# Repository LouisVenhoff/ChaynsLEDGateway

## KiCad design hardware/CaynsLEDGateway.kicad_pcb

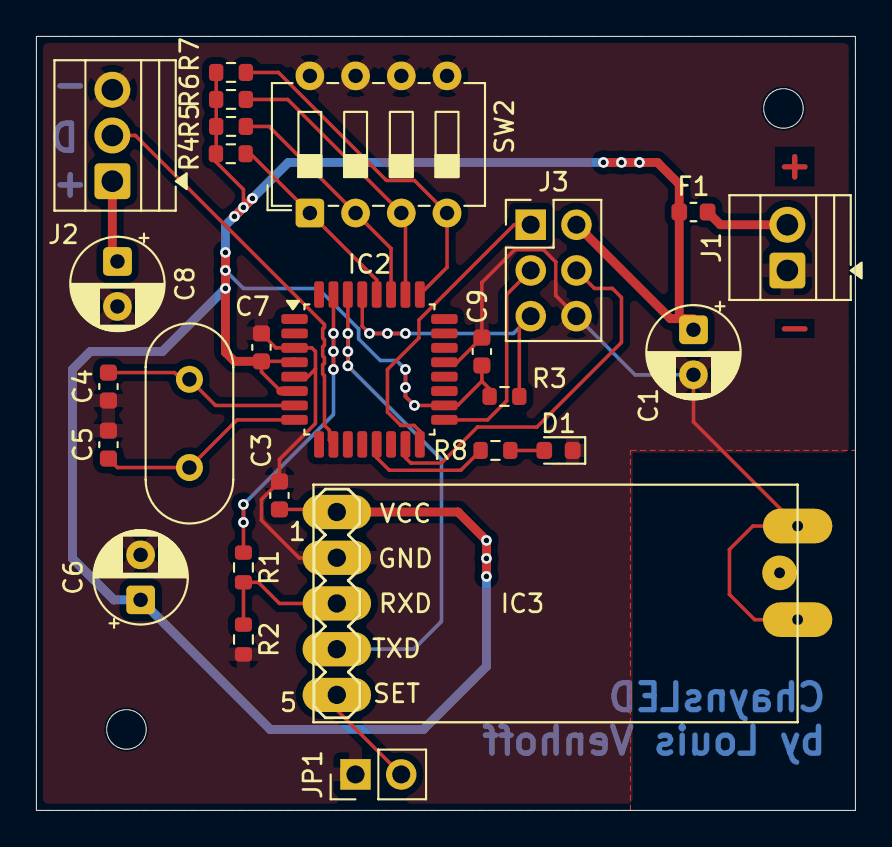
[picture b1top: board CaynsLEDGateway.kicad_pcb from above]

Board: 2 copper layers, 45.5 x 43.0 mm, 28 parts (0 on the bottom side), 21 nets.

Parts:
C1: 100uF; CP_Radial_D5.0mm_P2.50mm
C3, C7, C9: 100n; C_0603_1608Metric
C4, C5: 22pF; C_0603_1608Metric
C6, C8: 47uF; CP_Radial_D5.0mm_P2.50mm
D1: LED Red; LED_0603_1608Metric
F1: 1,5A; Fuse_0603_1608Metric
H1, H2: M2; MountingHole_2.2mm_M2
IC2: ATmega328P-A; TQFP-32_7x7mm_P0.8mm
IC3: HC-12; MA05-1
J1: Screw_Terminal_01x02; TerminalBlock_Xinya_XY308-2.54-2P_1x02_P2.54mm_Horizontal
J2: Screw_Terminal_01x03; TerminalBlock_Xinya_XY308-2.54-3P_1x03_P2.54mm_Horizontal
J3: Conn_02x03_Odd_Even; PinHeader_2x03_P2.54mm_Vertical
JP1: Jumper_2_Bridged; PinHeader_1x02_P2.54mm_Vertical
R1: 5,2k; R_0603_1608Metric
R2, R3, R4, R5, R6, R7: 10k; R_0603_1608Metric
R8: 150R; R_0603_1608Metric
SW2: SW_DIP_x04; SW_DIP_SPSTx04_Slide_6.7x11.72mm_W7.62mm_P2.54mm_LowProfile
Y1: 16Mhz; Crystal_HC18-U_Vertical

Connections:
+5V: C1.1, C3.2, C6.1, C7.1, C9.2, F1.1, IC2.4 (VCC), IC2.6 (VCC), IC2.18 (AVCC), IC3.1 (VCC), J3.2, R3.1, R4.1, R5.1, R6.1, R7.1
/AddressDip/A0: IC2.28 (PC5), R4.2, SW2.1
/AddressDip/A1: IC2.27 (PC4), R5.2, SW2.2
/AddressDip/A2: IC2.26 (PC3), R6.2, SW2.3
/AddressDip/A3: IC2.25 (PC2), R7.2, SW2.4
GND: C1.2, C3.1, C4.1, C5.2, C6.2, C7.2, C8.2, C9.1, D1.1 (K), IC2.3 (GND), IC2.5 (GND), IC2.21 (GND), IC3.2 (GND), IC3.GND (GND1), IC3.GND1, J1.1, J2.3, J3.6, JP1.1 (A), R2.2, SW2.5, SW2.6, SW2.7, SW2.8
unnamed: D1.2 (A), R8.1
unnamed: IC2.13 (PB1), R8.2
unnamed: IC2.15 (PB3), J3.4
unnamed: IC2.16 (PB4), J3.1
unnamed: IC2.17 (PB5), J3.3
unnamed: IC2.30 (PD0), IC3.4 (TXD)
unnamed: IC2.31 (PD1), R1.1
unnamed: IC2.10 (PD6), J2.2
unnamed: C4.2, IC2.7 (XTAL1/PB6), Y1.2
unnamed: C5.1, IC2.8 (XTAL2/PB7), Y1.1
unnamed: IC2.29 (~RESET/PC6), J3.5, R3.2
unnamed: IC3.3 (RXD), R1.2, R2.1
unnamed: IC3.5 (SET), JP1.2 (B)
unnamed: F1.2, J1.2
unnamed: C8.1, J2.1

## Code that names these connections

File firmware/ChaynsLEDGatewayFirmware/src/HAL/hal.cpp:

#include "hal.h"
#include <avr/io.h>

int init(){
    DDRB |= (1 << INT_LED);

    DDRC &= ~((1 << PC2) | (1 << PC3) | (1 << PC4) | (1 << PC5));

    return 0;
}


uint8_t readDeviceAddress(){
    return ~((PINC >> 2) & 0b00001111);
};

int switchInternalLED(bool state){
    uint8_t mask = 1 << INT_LED;

    if(state){
        PORTB |= mask;
    } else {
        PORTB &= ~mask;
    }

    return 0;
}
